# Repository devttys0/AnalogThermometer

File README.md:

Analog Thermometer
===================

A small, simple, low power circuit that turns practically any analog ammeter into an attractive thermometer, displaying temperatures from 0-70C with a typical accuracy of +-1 degree celcius.

  * One inch square PCB size
  * Low cost (single quantity [components](./digikey_bom.csv): $7, OSHPark PCB: $5)
  * Runs from a single 2.5-5.5V supply, typical current consumption <15uA (plus the analog ammeter's current requirements)
  * Easily adapted to work with nearly any ammeter by changing a single resistor, and/or adjusting a potentiometer

3D rendering of the PCB design:

A Cole DC ammeter displaying the lab temperature of 20 degrees Celcius:

Circuit Description
===================

The AnalogThermometer circuit is based around a Microchip MCP9700A temperature sensor. An LTC1541 op-amp is used as a differential amplifier to remove the 500mV offset voltage from the MCP9700A's output voltage. Finally, the differential amplifier controls a simple NPN current sink, whose current varies linearly with temperature; this drives the analog ammeter with a current that is proportional to the ambient temperature.

Circuit Construction
====================

Circuit construction is largely the same for any analog meter, with only two design questions that must be answered:

1. Do you want the MCP9700A temperature sensor to be a surface mount or a through-hole component?
2. What resistor value should be used for resistor R7 in order to accurately display the temperature on your analog meter?

Surface mount or through-hole?
------------------------------

Provisions have been made on the PCB for both the through-hole and surface mount versions of the MCP9700A temperature sensor. There is no technical advantage one way or the other, so the decision of which one to use is primarily determined by physical constraints / personal preference.

In the schematic and on the PCB, U2 is the through-hole version (TO-92 package) and U3 is the surface mount version (SOT-23). **Populate either U2 or U3, but not both!**

What value resistor do I use for R7?
------------------------------------

Different analog meters require different amounts of current for full-scale deflection of the meter's needle. The selection/adjustment of resistors R7/RV1 directly determines how much current is put through the analog meter for each degree of temperature change.

The easy way to set the correct amount of current is to simply not populate resistor R7 at all and adjust the potentiometer RV1 until the analog meter reads the correct temperature. If you choose this option, that's all you need to do and your work is done. The downsides to this however is that it requires fiddly adjustments, and will inevitably be less accurate than selecting a fixed resistor of the correct value.

The preferred method is to leave the potentiometer RV1 unpopulated and calculate exactly the correct amount of resistance required. Resistor R7 can then be populated with a fixed resistor of the appropriate value.

The amount of current that your analog meter requires is determined by the full-scale deflection current of your meter, and the scale printed on the meter's faceplate. Alan, W2AEW, has made some excellent videos on [finding the full-scale deflection current of a meter](https://www.youtube.com/watch?v=wbRx5cQZ8Ts&t=3m22s), as well as [printing custom scales for the face
plate](https://www.youtube.com/watch?v=wbRx5cQZ8Ts&t=13m09s). **His videos are highly recommended if you are not familiar with analog meters**.

Here is a simple example. This particular meter was manufactured with a scale of 0-50uA on the faceplate, which is ideal for our application as the temperature in degrees celcius can be read directly from the existing scale:

Having settled on a scale of 0-50, all that is left is to determine how much current is required to deflect the needle full-scale. Some analog meters will have this value conveniently printed on them:

The text `FS=50UADC` on this meter tells us that 50uA of direct current will deflect the meter to its full-scale position.

Unfortunately, the analog meter used in our example does not have this information printed on it, but it is easy to experimentally determine the full-scale current by placing a current meter in series between an adjustable voltage power supply and the analog meter. If you don't have an adjustable voltage source, a fixed voltage source with a variable resistor will work just as well:

Simply increase the power supply voltage until the needle is deflected full-scale, then read the current measured by the current meter. In this case, it is 25uA:

Since our scale ranges from 0 to 50 degrees, and the current required for a full-scale reading of 50 degrees is 25uA, we can calculate how much current is required to move the needle by one degree on our 0-50 scale:

```
25uA / 50 = 0.5uA
```

So we need the current to increase by 0.5uA for a one degree increase in temperature. The AnalogThermometer circuit increases the voltage across resistor R7 by 10mV for a one degree celcius increase, so ohm's law tells us that resistor R7 must be:

```
10mV / 0.5uA = 20,000
```

A 20k ohm resistor can be used for resistor R7. Resistors with tolerances of 1% or better are recommended.

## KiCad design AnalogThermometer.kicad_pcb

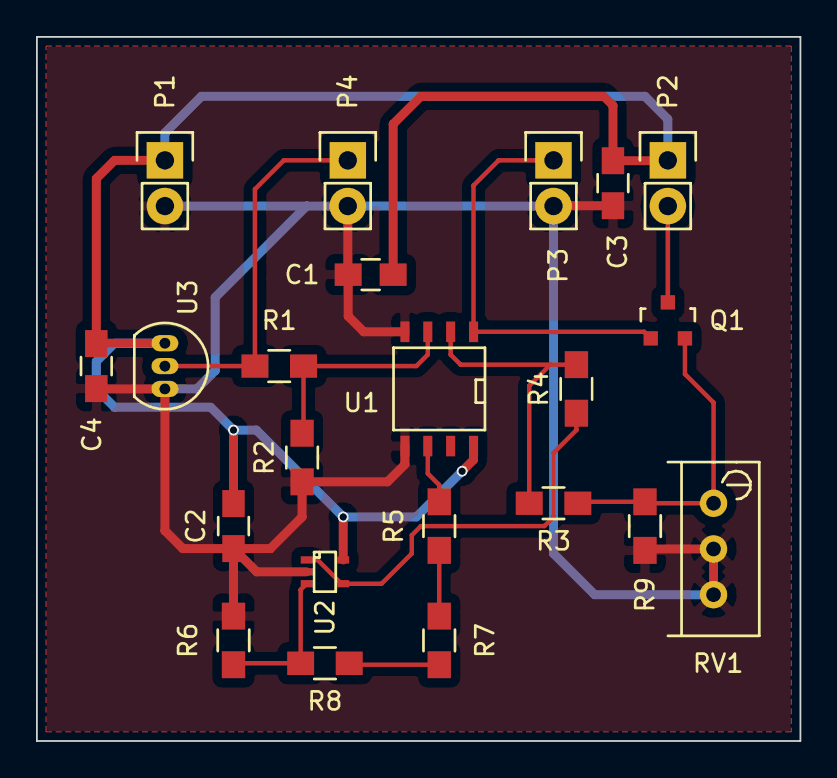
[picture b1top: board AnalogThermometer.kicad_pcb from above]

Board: 2 copper layers, 42.4 x 39.1 mm, 22 parts (0 on the bottom side), 13 nets.

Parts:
C1, C2, C3, C4: 0.1uF; C_0805_HandSoldering
P1: Power; Socket_Strip_Straight_1x02
P2: uA; Socket_Strip_Straight_1x02
P3: Vout; Socket_Strip_Straight_1x02
P4: Vtemp; Socket_Strip_Straight_1x02
Q1: MMBT3904; SOT-23
R1, R2, R3, R4, R5, R6: 1M; R_0805_HandSoldering
R7, R8: 200k; R_0805_HandSoldering
R9: 33.2k; R_0805_HandSoldering
RV1: 100k; Potentiometer_Bourns_3296W_3-8Zoll_Inline_ScrewUp
U1: LTC1541; SOIC-8-N
U2: MCP6V11; SC-70-5
U3: MCP9700A; TO-92_Inline_Narrow_Oval

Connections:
+5V: C1.2, C2.2, C3.2, C4.2, P1.1, P2.1, U1.8, U2.5, U3.1
GND: C1.1, C2.1, C3.1, C4.1, P1.2, P3.2, P4.2, R2.1, R6.1, R9.1, RV1.2, RV1.3, U1.4, U1.5, U2.2, U3.3
unnamed: P2.2, Q1.3
unnamed: P3.1, Q1.1, U1.1
unnamed: P4.1, R1.2, U3.2
unnamed: Q1.2, R3.1, R9.2, RV1.1
unnamed: R1.1, R2.2, U1.3
unnamed: R3.2, R4.2, U1.2
unnamed: R4.1, U2.1, U2.4
unnamed: R5.1, R7.1
unnamed: R5.2, U1.6
unnamed: R6.2, R8.2, U2.3
unnamed: R7.2, R8.1

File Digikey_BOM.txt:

4,490-1673-1-ND
1,MCP6V11UT-E/LTCT-ND
1,MMBT3904FSCT-ND
1,MCP9700A-E/TO-ND
1,490-2876-ND
1,311-33.2KCRCT-ND
6,YAG3361CT-ND
1,LTC1541IS8#PBF-ND
2,311-200KCRCT-ND

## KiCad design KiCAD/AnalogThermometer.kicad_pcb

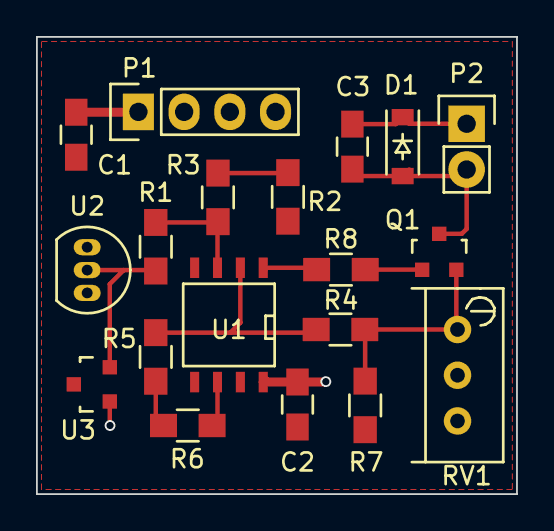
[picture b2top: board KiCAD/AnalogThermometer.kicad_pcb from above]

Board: 2 copper layers, 26.7 x 25.4 mm, 19 parts (0 on the bottom side), 12 nets.

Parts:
C1, C2, C3: 0.1uF; C_0805_HandSoldering
D1: 1N4148; SOD-123
P1: Power; Socket_Strip_Straight_1x04
P2: uA; Socket_Strip_Straight_1x02
Q1: MMBT3904; SOT-23
R1, R4: 1M; R_0805_HandSoldering
R2, R5: 2.2M; R_0805_HandSoldering
R3, R6: 200k; R_0805_HandSoldering
R7: 49.9k; R_0805_HandSoldering
R8: 100; R_0805_HandSoldering
RV1: 100k; Potentiometer_Bourns_3296W_3-8Zoll_Inline_ScrewUp
U1: LTC1541; SOIC-8-N
U2: MCP9700A; TO-92_Inline_Narrow_Oval
U3: MCP9700AT; SOT-23

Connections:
+5V: C1.2, C2.2, C3.2, D1.1, P1.1, P2.1, U1.8, U2.1, U3.1
GND: C1.1, C2.1, P1.4, R3.1, R7.1, RV1.2, RV1.3, U1.4, U1.5, U2.3, U3.3
unnamed: C3.1, D1.2, P2.2, Q1.3
unnamed: Q1.1, R8.1
unnamed: Q1.2, R4.1, R7.2, RV1.1
unnamed: R1.1, R2.2, U1.3
unnamed: R1.2, U2.2, U3.2
unnamed: R2.1, R3.2
unnamed: R4.2, R5.2, U1.2
unnamed: R5.1, R6.2
unnamed: R6.1, U1.6
unnamed: R8.2, U1.1

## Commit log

2016-04-12 Initial project check in
2016-05-04 Updated to rev 1.2
2016-05-04 Added images directory
2016-05-04 Added README
2016-05-04 Fixed README typo
2016-05-04 Removed unecessary file
2016-05-05 Added construction documentation
2016-05-05 Added image to documentation
2016-05-05 Updated documentation
2016-05-05 Added pictures
2016-05-05 Fixed typo
2016-05-15 Directory re-structure
2016-05-15 Minor update
2016-05-17 Updated board and gerbers to be 1x1 inch
